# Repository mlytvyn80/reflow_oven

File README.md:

# Reflow owen

Description

## Getting Started

The firmware can be compiled using make utility. 
```
make all
```

Some more make targets are supported, namely *all, clean, coff extcodd program, debug.*
Please consult the Makefile for usage details.

### Prerequisites

In order to compile the HEX-file you need to install the AVR toolchain. 

In Ubuntu/Debian Linux this can be done using the following command:
```
sudo apt-get install gcc-avr
```

To be able to flash the firmware you will need a driver AVR MCU programmer (for example [usbasp](https://www.fischl.de/usbasp/) ) and the 
driving program like [avrdude](https://www.nongnu.org/avrdude/).

avrdude is included in the most of Linux distribution. In Ubuntu/Debian you can issue:
```
sudo apt-get install avrdude
```

### Flashing the firmware
Connect the ISP head with your AVR MCU programmer, programmer to PC and flash the compiled HEX-file:
```
avrdude -c usbasp -p m32u4 -U flash:w:ovencon.hex
```

In order to configure MCU to work with external oscillator (in our case 16MHz quartz), it is necessary to
setup fuse bits.

It can be done by command:
```
avrdude -c usbasp -p m32u4 -U hfuse:w:0xdd:m -U lfuse:w:0xde:m -U efuse:w:0xcf:m
```

## Built With

* [GNU AVR toolchain](http://www.dropwizard.io/1.0.2/docs/) - The web framework used
* [avrdude](https://maven.apache.org/) - Dependency Management
* [usbasp](https://www.fischl.de/usbasp/) - AVR MCU programmer

## Authors

* **Daniel Strother** - *Initial work* - [danstrother.com](https://danstrother.com/2011/01/15/reflow-oven-controller/)
* **Oleg Artamonov** - *PCB Design*  - [olegart.ru](http://olegart.ru/wordpress/reflow-soldering/)
* **Mykhailo Lytvyn** - Collect all necessary build-related information together.

## License

The code is distributed "AS IS" under original License by Dan Strother (see header comments in source code).

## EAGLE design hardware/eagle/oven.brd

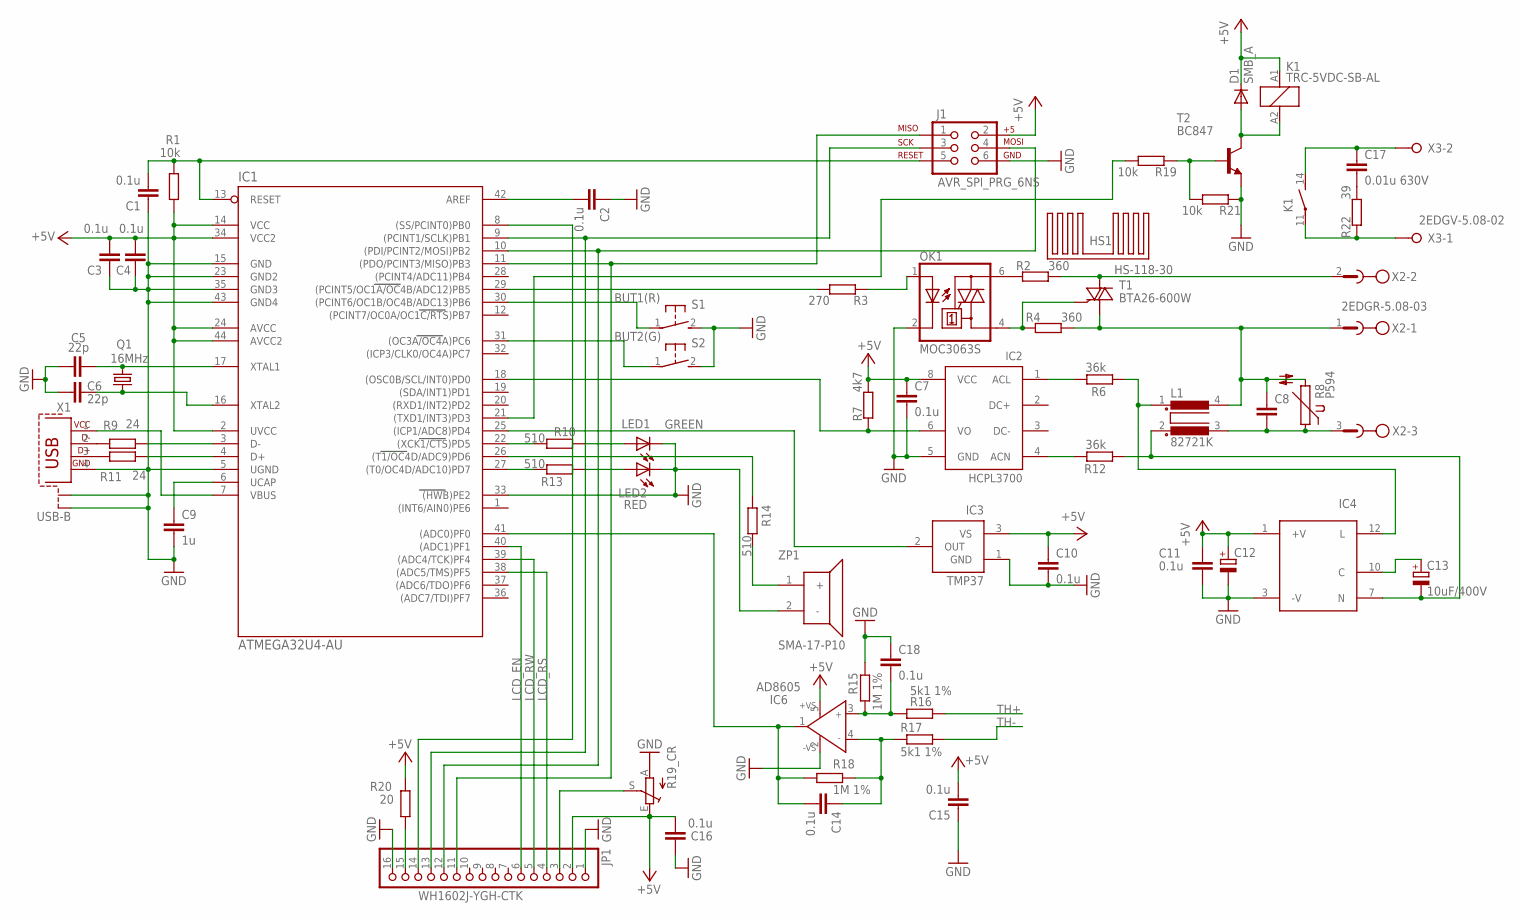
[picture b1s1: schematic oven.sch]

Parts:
C1, C2, C3, C4, C7, C10, C11, C14, C15, C16, C18: 0.1u; C0805R
C5, C6: 22p; C0805R
C8: C-EU102-054X133; C102-054X133
C9: 1u; C0805R
C12: CPOL-EUE3.5-8; E3,5-8
C13: 10uF/400V; E5-10,5
C17: 0.01u 630V; C102-043X133
D1: SMB_A; DO-214AC
HS1: HS-118-30; HS-118
IC1: ATMEGA32U4-AU; TQFP44
IC2: HCPL3700; DIL08
IC3: TMP37; TO92
IC4: PPM2.5-S12-05ELF; SIP12
IC6: AD8605; SOT23-5
J1: AVR_SPI_PRG_6NS; 2X3-NS
JP1: WH1602J-YGH-CTK; 1X16
K1: TRC-5VDC-SB-AL; TRC
L1: 82721K
LED1: GREEN; LED3MM
LED2: RED; LED3MM
OK1: MOC3063S; DIL6-SMD
Q1: 16MHz; HC49/S
R1, R19, R21: 10k; R0805R
R2, R4: 360; R2512
R3: 270; R0805R
R6, R12: 36k; R1206R
R7: 4k7; R0805R
R8: P594
R9, R11: 24; R0805R
R10, R13, R14: 510; R0805R
R15, R18: 1M 1%; R0805R
R16, R17: 5k1 1%; R0805R
R19_CR: TRIM_EU-CA6V; CA6V
R20: 20; R0805R
R22: 39; 0207/5V
S1, S2: 31-XX; B3F-31XX
T1: BTA26-600W; TOP3S-1
T2: BC847; SOT23
X1: USB-B; PN61729-S
X2: 2EDGR-5.08-03; W232-3
X3: 2EDGV-5.08-02; W237-132
ZP1: SMA-17-P10; SMA-17

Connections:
+5V: C3.2, C4.2, C7.1, C10.1, C11.1, C12.+, C15.2, C16.2, D1.C, IC1.2 (UVCC), IC1.14 (VCC), IC1.24 (AVCC), IC1.34 (VCC2), IC1.44 (AVCC2), IC2.8 (VCC), IC3.3 (VS), IC4.1 (+V), IC6.5 (+VS), J1.2, JP1.2, K1.A1 (1), R1.1, R7.2, R19_CR.E, R20.1
BUT1(R): IC1.30 ((PCINT6/OC1B/OC4B/ADC13)PB6), S1.1
BUT2(G): IC1.31 ((OC3A/OC4A)PC6), S2.1
GND: C1.1, C2.1, C3.1, C4.1, C5.1, C6.1, C7.2, C9.2, C10.2, C11.2, C12.-, C15.1, C16.1, C18.1, IC1.5 (UGND), IC1.15 (GND), IC1.23 (GND2), IC1.33 ((HWB)PE2), IC1.35 (GND3), IC1.43 (GND4), IC2.5 (GND), IC3.1 (GND), IC4.3 (-V), IC6.2 (-VS), J1.6, JP1.1, JP1.16, LED1.K (C), LED2.K (C), OK1.2 (C), R15.2, R19_CR.A, R21.1, S1.2 (S), S2.2 (S), T2.2 (E), X1.4, X1.S1, X1.S2, ZP1.2 (-)
LCD_D4: IC1.11 ((PDO/PCINT3/MISO)PB3), J1.1, JP1.11
LCD_D5: IC1.10 ((PDI/PCINT2/MOSI)PB2), J1.4, JP1.12
LCD_D6: IC1.9 ((PCINT1/SCLK)PB1), J1.3, JP1.13
LCD_D7: IC1.8 ((SS/PCINT0)PB0), JP1.14
LCD_EN: IC1.40 ((ADC1)PF1), JP1.6
LCD_RS: IC1.38 ((ADC5/TMS)PF5), JP1.4
LCD_RW: IC1.39 ((ADC4/TCK)PF4), JP1.5
unnamed: C9.1, IC1.6 (UCAP)
unnamed: R9.1, X1.2
unnamed: R11.1, X1.3
unnamed: IC1.3 (D-), R9.2
unnamed: IC1.4 (D+), R11.2
unnamed: IC1.7 (VBUS), X1.1
unnamed: IC1.18 ((OSC0B/SCL/INT0)PD0), IC2.6 (VO), R7.1
unnamed: C5.2, IC1.17 (XTAL1), Q1.2
unnamed: C6.2, IC1.16 (XTAL2), Q1.1
unnamed: IC1.29 ((PCINT5/OC1A/OC4B/ADC12)PB5), R3.2
unnamed: C1.2, IC1.13 (RESET), J1.5, R1.2
unnamed: C2.2, IC1.42 (AREF)
unnamed: C17.2, R22.2
unnamed: OK1.1 (A), R3.1
unnamed: OK1.6 (A2), R2.1
unnamed: OK1.4 (A1), R4.1, T1.G
unnamed: R2.2, T1.A2, X2.2
unnamed: IC4.12 (L), L1.1, R6.1
unnamed: JP1.15, R20.2
unnamed: IC1.25 ((ICP1/ADC8)PD4), IC3.2 (OUT)
unnamed: IC2.4 (ACN), R12.2
unnamed: C14.2, IC1.41 ((ADC0)PF0), IC6.1 (OUT), R18.1
unnamed: C18.2, IC6.3 (IN+), R15.1, R16.1
unnamed: C14.1, IC6.4 (IN-), R17.1, R18.2
unnamed: IC2.1 (ACL), R6.2
unnamed: LED1.A, R10.1
unnamed: C13.+, IC4.10 (C)
unnamed: IC1.22 ((XCK1/CTS)PD5), R10.2
unnamed: IC1.26 ((T1/OC4D/ADC9)PD6), R14.1
unnamed: IC1.27 ((T0/OC4D/ADC10)PD7), R13.2
unnamed: LED2.A, R13.1
unnamed: C13.-, IC4.7 (N), L1.2 (3), R12.1
unnamed: C8.1, L1.4 (2), R4.2, R8.2, T1.A1, X2.1
unnamed: C8.2, L1.3 (4), R8.1, X2.3
unnamed: JP1.3, R19_CR.S
unnamed: D1.A, K1.A2 (2), T2.3 (C)
unnamed: R19.1, R21.2, T2.1 (B)
unnamed: R14.2, ZP1.1 (+)
unnamed: C17.1, K1.14 (S), X3.2
unnamed: IC1.21 ((TXD1/INT3)PD3), R19.2
unnamed: K1.11, R22.1, X3.1
TH+: R16.2
TH-: R17.2

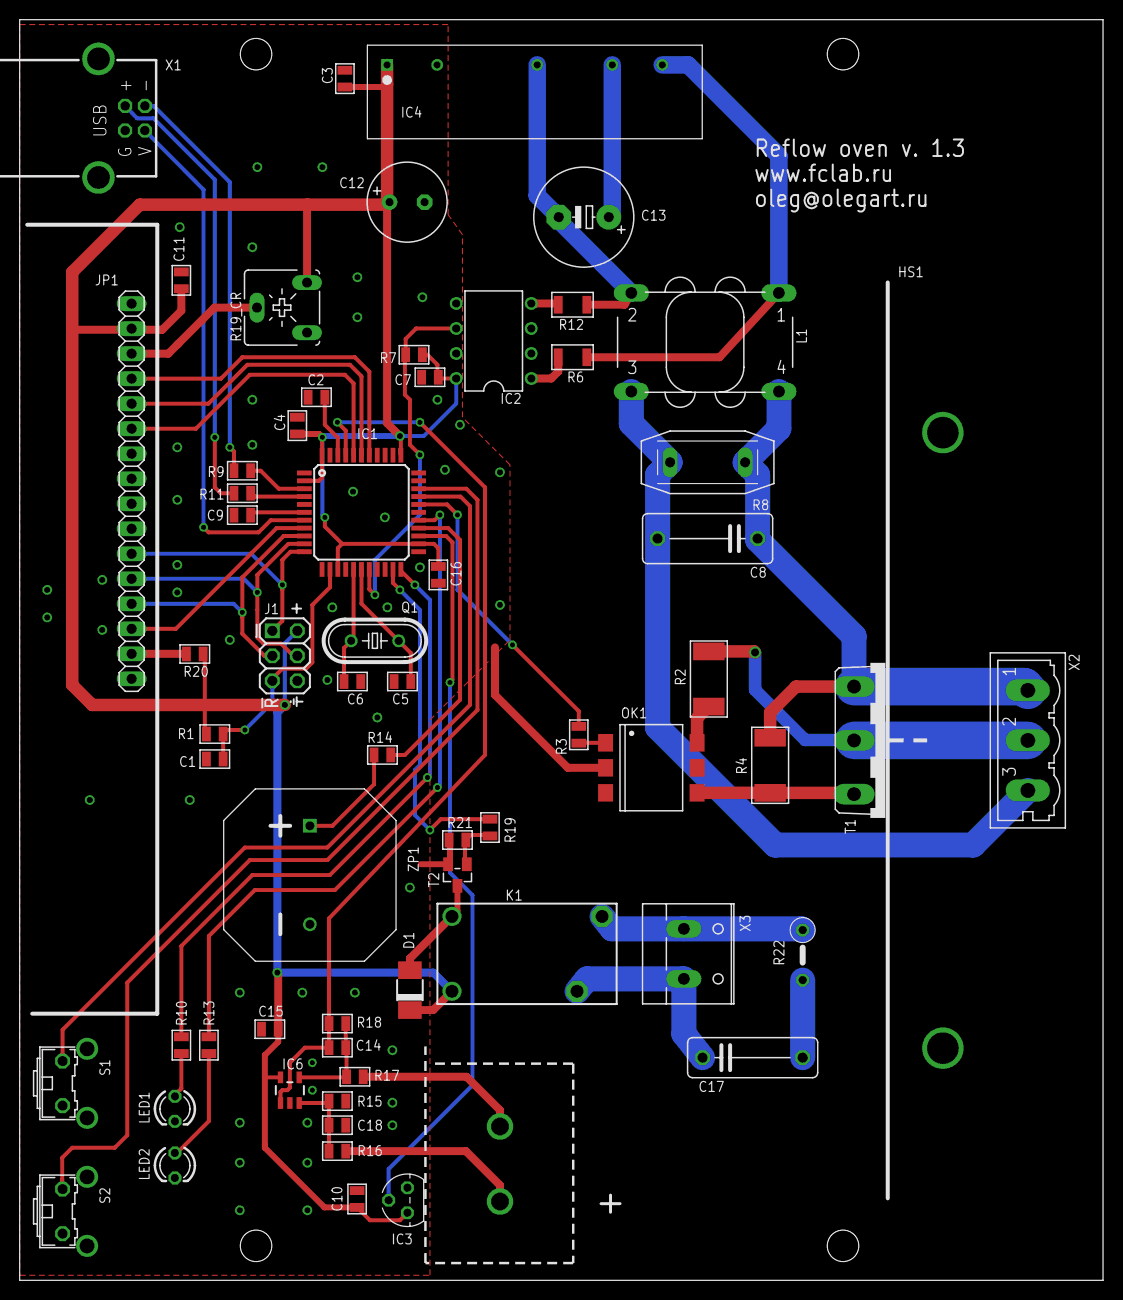
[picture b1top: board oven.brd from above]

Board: 2 copper layers, 110.0 x 128.0 mm, 63 parts (0 on the bottom side), 52 nets.

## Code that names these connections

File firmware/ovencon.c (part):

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#define relay_on() PORTD |= _BV(3)
#define relay_off() PORTD &= ~_BV(3)

#define button1() !(PINB & (1<<PB6))
#define button2() !(PINC & (1<<PC6))

uint32_t Boot_Key __attribute__ ((section (".noinit")));
#define MAGIC_BOOT_KEY            0xDC42ACCA
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    SPCR &= ~(1<<SPE);

    // Pullups
    PINB |= (1<<PB6);
    PINC |= (1<<PC6)|(1<<PC7);

    // LED status lights
    DDRD |= (1<<PD5)|(1<<PD6)|(1<<PD7);
    DDRD |= (1<<PD3);

    rled_on();
    relay_off();
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
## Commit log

2018-06-18 Initial release
2018-06-20 Changed folder structure; added PCB Eagle CAD files and schematic
2018-11-07 -All objects with PROGMEM attribute declared as const; -usb_serial: fix usb_serial_set_control function
2018-11-07 changed README
2018-11-07 Fold duplicated code into functions
2018-11-09 Added oven_command struct
2018-11-09 Introduced simple binary data exchange protocol
2018-11-09 Fixed lcd_put_animate

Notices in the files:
firmware/ovencon.c:
Copyright (c) 2011, Daniel Strother < http://danstrother.com/ >
All rights reserved.
